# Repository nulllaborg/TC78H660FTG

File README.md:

# TC78H660FTG
单路PWM驱动芯片，替代TB6612FNG芯片

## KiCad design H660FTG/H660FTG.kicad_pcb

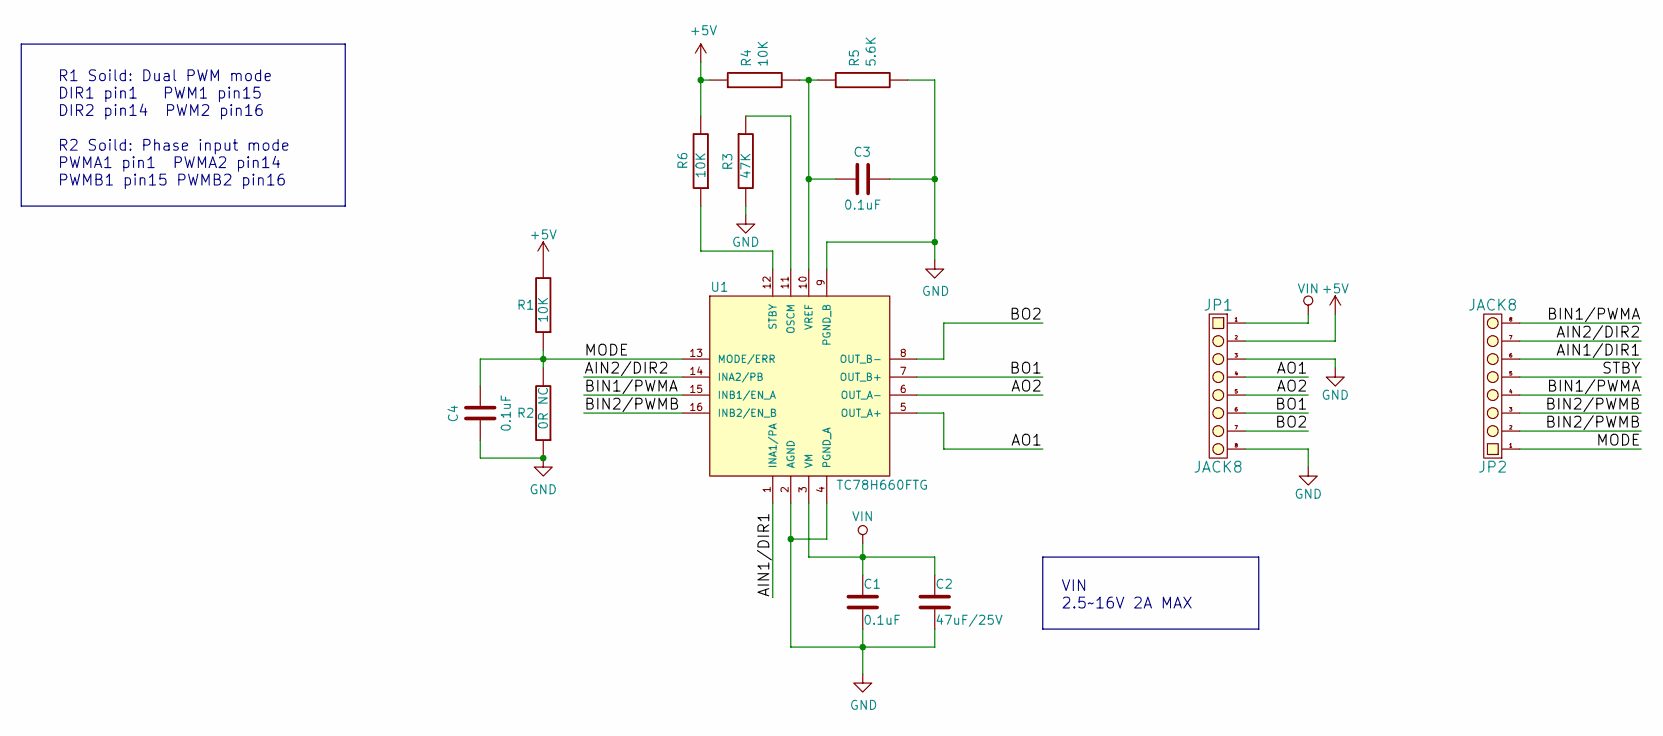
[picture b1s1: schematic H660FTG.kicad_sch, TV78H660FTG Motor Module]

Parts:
C1, C3, C4: 0.1uF; C_0603
C2: 47uF/25V; CP_EIA-3528-12_Kemet-T_Pad1.50x2.35mm_HandSolder
JP1, JP2: JACK8; DIP_8PIN_2.54mm_Stamp
R1, R4, R6: 10K; R_0603
R2: 0R NC; R_0603
R3: 47K; R_0603
R5: 5.6K; R_0603
U1: TC78H660FTG; QFN-16-1EP_3x3mm_P0.5mm_EP1.9x1.9mm

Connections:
+5V: JP1.2, R1.2, R4.1, R6.2
/AIN1/DIR1: JP2.6, U1.1 (INA1/PA)
/AIN2/DIR2: JP2.7, U1.14 (INA2/PB)
/AO1: JP1.4, U1.5 (OUT_A+)
/AO2: JP1.5, U1.6 (OUT_A-)
/BIN1/PWMA: JP2.4, JP2.8, U1.15 (INB1/EN_A)
/BIN2/PWMB: JP2.2, JP2.3, U1.16 (INB2/EN_B)
/BO1: JP1.6, U1.7 (OUT_B+)
/BO2: JP1.7, U1.8 (OUT_B-)
/MODE: C4.2, JP2.1, R1.1, R2.2, U1.13 (MODE/ERR)
/STBY: JP2.5
GND: C1.2, C2.2, C3.2, C4.1, JP1.3, JP1.8, R2.1, R3.2, R5.2, U1.2 (AGND), U1.4 (PGND_A), U1.9 (PGND_B), U1.17
unnamed: C3.1, R4.2, R5.1, U1.10 (VREF)
unnamed: R3.1, U1.11 (OSCM)
unnamed: R6.1, U1.12 (STBY)
VIN: C1.1, C2.1, JP1.1, U1.3 (VM)

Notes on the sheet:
VIN 2.5~16V 2A MAX
R1 Soild: Dual PWM mode DIR1 pin1 PWM1 pin15 DIR2 pin14 PWM2 pin16 R2 Soild: Phase input mode PWMA1 pin1 PWMA2 pin14 PWMB1 pin15 PWMB2 pin16

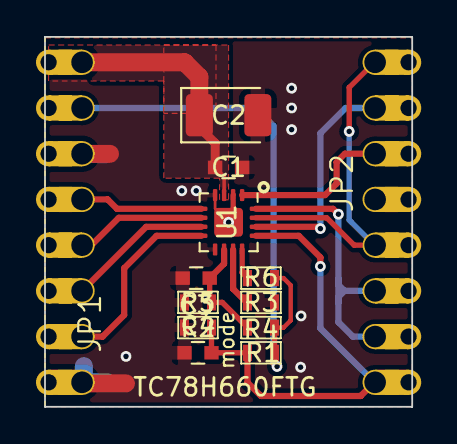
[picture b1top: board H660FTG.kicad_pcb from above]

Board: 2 copper layers, 20.4 x 20.5 mm, 13 parts (0 on the bottom side), 15 nets.

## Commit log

2022-09-24 add hw and doc
2022-11-18 Redesign PCB board
2022-11-18 修改3D
